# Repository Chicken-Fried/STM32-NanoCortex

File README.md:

<div align="center">

# ⚡ NanoCortex-F042
### by CaveRover

**Minimalist ARM Cortex-M0 development board — 20 mm × 38.5 mm, native USB-C, crystal-less**

[🇫🇷 Version française](README_FR.md) · [📄 Schematic (PDF)](arm_tiny_pcb_sch.pdf) · [🧰 Getting started](#getting-started) · [📌 Pinout](#pinout)

</div>

---

A practical, standalone 32-bit development board (**20 mm × 38.5 mm**), inspired by the minimalist philosophy and straightforward nature of the Arduino ATtiny, but optimized for comfortable benchtop development (*devboard*). Powered by the **STM32F042** (ARM Cortex-M0) with native crystal-less USB-C, a **TVS-protected** USB input and a **ceramic-only 3.3 V power stage**.

---

## 🌟 Why This Project?

This board was born at the intersection of academic learning, curiosity, and maker passion:

1. **Bridging Theory and Practice:** Taking electronic engineering coursework (schematic design, component selection, signal integrity, PCB layout) and applying it to a tangible, physical board.
2. **Stepping into 32-bit Microcontrollers:** Moving beyond traditional 8-bit platforms (AVR, ATtiny) into the modern ARM Cortex ecosystem.
3. **Fun & Hobby:** A passion-driven learning playground to experiment with USB stacks, low-power modes, and embedded programming.
4. **Giving Back to Open Source:** Providing a clean, accessible, and minimal reference design for students, hobbyists, and makers.
5. **Real-World Project Stepping Stone:** Serving as the core validation platform for three concrete engineering builds: a dedicated **drone telemetry/control subsystem**, an **audio synthesizer with active analog op-amp (AOP) filtering**, and a **digitally controlled $\ge$ 40W USB-PD / Buck converter power stage**.

---

## ✨ Key Features

* **🧠 Brain:** STMicroelectronics **STM32F042F6P6** (ARM Cortex-M0 @ 48 MHz, 32 KB Flash, 6 KB RAM).
* **🔌 Crystal-less USB-C:** Employs the internal 48 MHz oscillator (`HSI48`) paired with Clock Recovery System (`CRS`) synchronized directly to USB frames—**zero external crystal required**.
* **🚀 Zero-Programmer Flashing (Native DFU):** Factory ROM USB bootloader built-in. Hold the `BOOT` button, plug in the USB-C cable, and flash directly with `STM32CubeProgrammer` or `dfu-util`—no ST-Link or external programmer strictly required!
* **📐 Compact Devboard Layout (20 mm × 38.5 mm):** Slim form factor with two 9-pin I/O headers on the long sides, and the `BOOT` / `RESET` buttons on each side of the USB-C connector.
* **🛡️ Enhanced USB Protection:** **SD05-01FTG** TVS diode on `VBUS`, **USBLC6-2SC6** on the data lines and a 500 mA resettable polyfuse.
* **⚡ Stable 3.3 V:** **ME6211C33M5G-N** low-dropout, low-quiescent-current LDO, stable with small **ceramic capacitors** (no more tantalum).
* **💡 Two Indicator LEDs:** a red `3V3` power LED and an addressable **WS2812B-2020-V6** RGB `STATUS` LED driven from `PA0` (native 3.3 V operation with dedicated 100 nF decoupling capacitor `C8`).
* **🎛️ Dual Tactile Buttons:** On-board `RESET` and `BOOT` tactile switches for instant programming mode entry.
* **🛰️ CaveRover Branding:** Features the official 8-bit pixel art CaveRover rover silkscreen emblem and futuristic Anurati typographic markings directly on the PCB.
* **🛠️ Open-Source & DIY Ready:** Standard 2-layer PCB design rules for affordable fabrication and assembly (e.g. JLCPCB).

---

## 📋 Specifications

| Parameter | Specification |
| :--- | :--- |
| **Microcontroller** | STM32F042F6P6 (TSSOP-20) |
| **Core Architecture** | ARM 32-bit Cortex-M0 @ up to 48 MHz |
| **Flash / SRAM** | 32 KB Flash / 6 KB SRAM |
| **Operating Voltage** | 3.3 V logic (Dual power rails exposed: 5 V via USB-C + 3.3 V regulated) |
| **3.3 V Regulator** | ME6211C33M5G-N (LDO, SOT-23-5) with 2 ceramic capacitors (X7R, 25 V, 0805) |
| **Input Protection** | SD05-01FTG (TVS) + USBLC6-2SC6 (USB data lines) + 500 mA polyfuse |
| **USB Interface** | USB 2.0 Full Speed (12 Mbps) over USB-C |
| **User I/O** | 12 GPIOs on 2.54 mm headers (9 general-purpose, 1 shared with BOOT0, 2 shared with SWD) + dedicated hardware `NRST` |
| **Programming & Debug** | Native USB DFU (ROM bootloader) or full 4-wire SWD (`GND`, `NRST`, `SWDIO`, `SWCLK`) |
| **On-board LEDs** | Red `3V3` power LED + WS2812B-2020-V6 RGB status LED (`PA0`) with 100 nF decoupling capacitor |
| **Dimensions** | **20 mm × 38.5 mm** |

---

## 📌 Pinout

The board has two 9-pin headers (`J1` on the left, `J2` on the right) and a 2 × 2 power header (`J3`) at the bottom edge.

| Header | Pin | Signal | MCU pin | Primary & Alternate Functions / Notes |
| :---: | :---: | :--- | :--- | :--- |
| **J1** | 1 | `5V` | – | 5.0 V power rail (VBUS post-polyfuse `F1`, up to 500 mA for drones/op-amps) |
| | 2 | `GPIO1` | `PB8` | Shared with `BOOT0` (10 kΩ pull-down). **Do not pull HIGH at boot!** |
| | 3 | `GPIO2` | `PF0` | `OSC_IN` / I2C1_SDA |
| | 4 | `GPIO3` | `PF1` | `OSC_OUT` / I2C1_SCL |
| | 5 | `GPIO5` | `PA1` | `ADC_IN1` / TIM2_CH2 / EVENTOUT |
| | 6 | `GPIO6` | `PA2` | `USART2_TX` / `ADC_IN2` / TIM15_CH1 / TIM2_CH3 |
| | 7 | `GPIO7` | `PA3` | `USART2_RX` / `ADC_IN3` / TIM15_CH2 / TIM2_CH4 |
| | 8 | `GPIO8` | `PA4` | `ADC_IN4` / SPI1_NSS / TIM14_CH1 |
| | 9 | `GND` | – | Ground |
| **J2** | 1 | `3V3` | – | 3.3 V regulated power rail |
| | 2 | `GPIO9` | `PA5` | `ADC_IN5` / SPI1_SCK |
| | 3 | `GPIO10` | `PA6` | `ADC_IN6` / SPI1_MISO / TIM3_CH1 / TIM16_CH1 |
| | 4 | `GPIO11` | `PA7` | `ADC_IN7` / SPI1_MOSI / TIM3_CH2 / TIM14_CH1 / TIM17_CH1 |
| | 5 | `GPIO12` | `PB1` | `ADC_IN9` / TIM3_CH4 / TIM14_CH1 |
| | 6 | `GND` | – | Ground |
| | 7 | `NRST` | Pin 4 | Hardware Reset line (supports ST-Link "Connect Under Reset" and remote reset button) |
| | 8 | `GPIO15` | `PA13` | `SWDIO` (SWD Data) / IR_OUT / USB_NOE |
| | 9 | `GPIO16` | `PA14` | `SWCLK` (SWD Clock) / USART2_TX |
| **J3** | 1–4 | `3V3` / `GND` | – | 2 × 2 header: 2 × `3V3`, 2 × `GND` (auxiliary power breakout) |

> ⚠️ **Important Note on `PB8 / BOOT0` (`GPIO1`):** Pin 1 of the TSSOP-20 package is shared between `BOOT0` and `PB8`. It is pulled down to GND via $R_7$ (10 kΩ) for normal Flash execution. Any external circuitry attached to `GPIO1` that pulls this pin HIGH at reset will force the microcontroller into native USB DFU bootloader mode.
>
> 💡 **Internal Signals & ADC Allocation:**
> * `PA0` is dedicated internally to the **WS2812B-2020-V6** RGB status LED via $R_6$ (330 Ω). Consequently, analog channel `ADC_IN0` is reserved for on-board LED operation. **7 external ADC channels** remain freely available on the headers (`PA1` to `PA7`).
> * `NRST` is wired to the tactile `RESET` button with a 100 nF debounce capacitor and routed to `J2` pin 7 for full debugger control.
>
> 🔌 **Serial Communication (`USART1` vs `USART2`):**
> * For user serial communication (e.g. drone CRSF/SBUS telemetry, debug console, GPS), **use `USART2` (`PA2`/`PA3`) on header `J1`**.
> * On the STM32F042 TSSOP-20 package, `USART1` (`PA9`/`PA10`) shares physical pins 17 & 18 with native USB Full-Speed (`PA11`/`PA12`, `USB_DM`/`USB_DP`). When USB is active, `USART1` cannot be used simultaneously.

---

## 🛠️ Hardware Overview

> 🔎 **Click the schematic to open the full-resolution vector PDF** → [`arm_tiny_pcb_sch.pdf`](arm_tiny_pcb_sch.pdf)

### Power & Protection
* **USB-C Input:** Standard Type-C receptacle (GT-USB-7025) with dual 5.1 kΩ pull-downs on `CC1`/`CC2` for universal charger and PC host compatibility.
* **TVS Diode (SD05-01FTG, D1):** Clamps ESD and surge events on `VBUS` (5 V) before they can reach the rest of the board.
* **Polyfuse (F1, 500 mA):** Resettable fuse between `VBUS` and the 5 V rail.
* **USB Data Protection (USBLC6-2SC6, U3):** Low-capacitance ESD protection on `D+` / `D-`, preserving Full-Speed signal integrity.
* **LDO Regulator (ME6211C33M5G-N, LDO1):** 5 V → 3.3 V, low dropout and very low quiescent current.
* **Ceramic-Only Capacitors:** Tantalum capacitors were replaced by **X7R ceramic capacitors** (`C1` 2.2 µF, `C2` 1 µF, 25 V, 0805) around the regulator: more stable with this LDO, smaller, non-polarized, and free of tantalum failure modes (inrush / surge).
* **Decoupling:** `C3` 100 nF, `C4` 4.7 µF, `C5` 10 nF and `C6` 1 µF placed close to the `VDD` / `VDDA` pins.

### Signal Routing
* **Differential USB Pair:** Matched $D^+$ and $D^-$ traces routed side-by-side with an unbroken ground reference plane on the bottom layer to maintain high signal integrity.

---

## 🧾 Key Components

| Ref | Part | Function |
| :--- | :--- | :--- |
| U1 | STM32F042F6P6 | Microcontroller (TSSOP-20) |
| LDO1 | ME6211C33M5G-N | 3.3 V LDO regulator (SOT-23-5) |
| U3 | USBLC6-2SC6 | ESD protection for USB data lines |
| D1 | SD05-01FTG | 5 V TVS diode on `VBUS` (SOD-323) |
| F1 | JK-SMD0603-050-6 | 0603 resettable fuse (500 mA) |
| USB1 | GT-USB-7025 | USB Type-C receptacle |
| SW1 / SW2 | SKRKAEE020 | `RESET` / `BOOT` tactile switches |
| LED1 | 16-213/BHC-AN1P2/3T | Red `3V3` power LED |
| LED2 | WS2812B-2020-V6 | RGB `STATUS` LED (addressable) |
| J1 / J2 / J3 | 1×9 / 1×9 / 2×2 pin headers | I/O and power headers |

---

## 📝 Revision History

| Change | Before | Now |
| :--- | :--- | :--- |
| **Board size** | 26 mm × 36 mm | **20 mm × 38.5 mm** |
| **LDO regulator** | XBL1117-3.3 (SOT-89) | **ME6211C33M5G-N** (SOT-23-5) |
| **Regulator capacitors** | Tantalum (EIA-3528) | **X7R ceramic (0805)** |
| **5 V input protection** | Fuse only | Fuse + **SD05-01FTG TVS diode** |

---

## 💻 Getting Started & Programming

### 1. Entering Native USB DFU Mode
No external probe needed:
1. Hold down the **BOOT** button.
2. Press and release the **RESET** button (or plug the USB-C cable into your PC).
3. Release the **BOOT** button.
4. Your computer now recognizes the device as an **STM32 BOOTLOADER** in DFU mode.

### 2. Flashing
Flash compiled `.bin` or `.hex` firmware using your tool of choice:
* **STM32CubeProgrammer** (GUI / CLI)
* **dfu-util:**
  ```bash
  dfu-util -a 0 -d 0483:df11 --dfuse-address 0x08000000 -D firmware.bin
  ```
* **SWD (optional):** connect an ST-Link to `GND`, `3V3`, `PA13` (`SWDIO`) and `PA14` (`SWCLK`) on `J1` / `J2`.

### 3. Firmware Support
* **STM32CubeIDE / Keil / IAR:** Native C/C++ development with STM32 HAL / LL drivers.
* **PlatformIO & Arduino:** Fully compatible via the official [STM32duino Core](https://github.com/stm32duino/Arduino_Core_STM32).

---

## 📁 Repository Content

| File / Folder | Description |
| :--- | :--- |
| [`arm_tiny_pcb.kicad_pro`](arm_tiny_pcb.kicad_pro) | KiCad project (open this one) |
| [`arm_tiny_pcb.kicad_sch`](arm_tiny_pcb.kicad_sch) | KiCad schematic |
| [`arm_tiny_pcb.kicad_pcb`](arm_tiny_pcb.kicad_pcb) | KiCad PCB layout |
| [`arm_tiny_pcb_sch.pdf`](arm_tiny_pcb_sch.pdf) | Schematic export (PDF) |
| [`arm_tiny_pcb.jpg`](arm_tiny_pcb.jpg) | 3D render of the board (full size) |
| [`docs/`](docs) | Images used in this README (top view, bottom view, 3D perspective, schematic preview, branding) |
| [`NanoCortex.kicad_sym`](NanoCortex.kicad_sym) | Project symbol library |
| [`NanoCortex.pretty/`](NanoCortex.pretty) | Project footprint library |
| [`NanoCortex.3dshapes/`](NanoCortex.3dshapes) | 3D models (`.wrl`) for the project footprints |
| `sym-lib-table`, `fp-lib-table` | Project library tables (paths relative to the project) |

> 📦 **Libraries:** everything needed to open the project is included. The `NanoCortex` libraries are registered automatically when you open `arm_tiny_pcb.kicad_pro` with **KiCad 10**.

---

## 🎯 Roadmap & Target Application Projects

This board serves as the prototyping brain for three dedicated embedded hardware projects:

### 🛸 Track 1: Lightweight Drone Subsystem & Telemetry Board
Using the NanoCortex-F042 as an embedded flight module or motor/sensor companion node:
- [ ] **Sensor Interface:** High-rate 6-axis IMU (gyro/accelerometer via SPI/I2C) readout on hardware timer interrupts.
- [ ] **Actuator Control:** Multi-channel high-speed motor control signals (OneShot / DShot / PWM at 400 Hz+).
- [ ] **Telemetry & Communication:** Real-time bi-directional link over serial UART (`USART2` running CRSF / SBUS / MSP protocol).
- [ ] **Custom PCB Spin:** Layout of a dedicated, miniaturized drone PCB integrating motor drivers and power management.

### 🎛️ Track 2: Hybrid USB-MIDI Synthesizer & Analog Op-Amp Audio Lab
A hands-on project to master operational amplifiers (Op-Amps / AOP) and USB communication without requiring heavy DSP:
- [ ] **USB-MIDI Communication:** Native class-compliant USB-MIDI device stack (plug-and-play with DAWs, keyboards, and PCs with zero drivers).
- [ ] **Sound Generation:** Multi-waveform oscillator (sawtooth, square, triangle, wavetable) generated via high-frequency hardware PWM / DMA.
- [ ] **Active Op-Amp Reconstruction Filter:** 2nd- or 4th-order active low-pass filter (Sallen-Key / Rauch topology) to smooth PWM into clean analog audio.
- [ ] **Analog Processing & Overdrive Stage:** Soft-clipping diode distortion stage within the op-amp feedback loop (classic overdrive pedal architecture) with active gain control.
- [ ] **Active Tone Control & Output Stage:** Active Baxandall bass/treble tone stack and low-impedance audio buffer for headphones or line-level output.

### ⚡ Track 3: Digitally-Controlled Buck Converter & 40W+ USB-PD Lab
A hands-on power electronics project to master switch-mode power supplies (Buck converters), op-amp feedback injection, and USB Power Delivery:
- [ ] **Synchronous Buck Stage:** Design of an external 24 V DC → 5 V–20 V / 3 A step-down converter (MOSFET selection, inductor saturation $I_{sat}$, and low-ESR ripple filtering).
- [ ] **Op-Amp Feedback Injection:** Dynamic voltage margin/target control via active op-amp summing into the Buck controller's feedback (`FB`) node.
- [ ] **USB-PD PHY Communication (FUSB302B):** I2C control of a dedicated USB-PD Source controller to negotiate 5 V, 9 V, 15 V, and 20 V profiles with laptops and phones.
- [ ] **Power Telemetry & Safety:** Real-time $V_{out}$ / $I_{out}$ monitoring via STM32 12-bit ADC, over-current/over-voltage shutdown, and $V_{BUS}$ power-switch control.

### 🧪 Board Validation Milestones
- [x] KiCad 10 schematic design & 2-layer PCB layout with matched USB differential pairs.
- [x] Hardware Revision: 20 mm × 38.5 mm form factor, TVS protection diode, ME6211 LDO, and MLCC ceramic capacitors.
- [ ] PCB fabrication and prototype SMD assembly.
- [ ] USB DFU bootloader and crystal-less CRS clock verification.
- [ ] 3.3 V power rail validation (ripple, stability, and transient response under load).

---

## 🤝 Contributing & Feedback

Suggestions, questions, and PRs are very welcome! Whether you are a student exploring embedded design or an experienced engineer with layout tips, feel free to open an **Issue** or submit a **Pull Request**.

---

## 📜 License

This hardware design (schematics, PCB layout, footprints, and 3D models) is licensed under the **[CERN Open Hardware Licence Version 2 – Strongly Reciprocal (CERN-OHL-S v2)](LICENSE)**.

> ⚖️ **Reciprocal Sharing:** You are free to study, modify, build, and distribute this board. If you distribute modified versions or products based on this design, you must make the complete modified source files available under the same **CERN-OHL-S v2** license.

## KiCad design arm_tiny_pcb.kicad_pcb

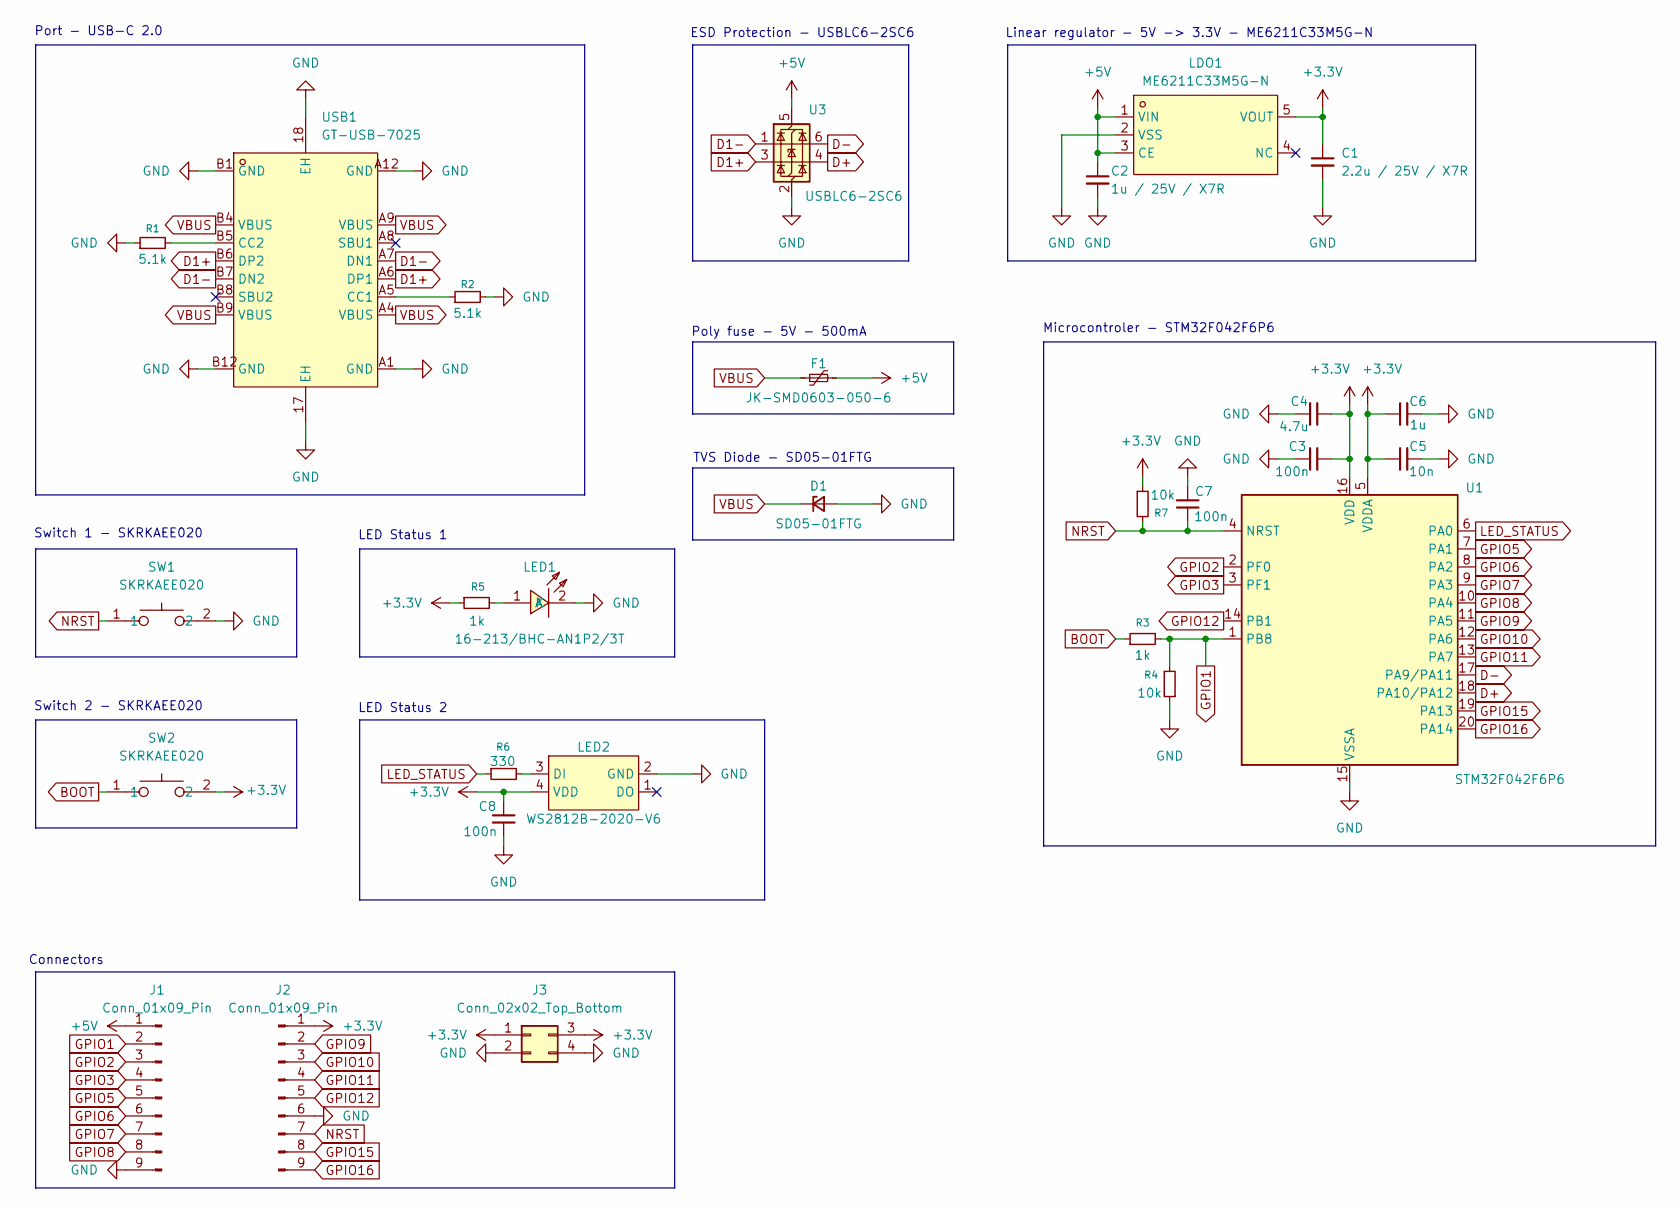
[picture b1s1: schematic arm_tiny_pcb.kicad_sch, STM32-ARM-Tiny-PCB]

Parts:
C1: 2.2u / 25V / X7R; C_0805_2012Metric; LCSC Part C22409262
C2: 1u / 25V / X7R; C_0805_2012Metric; LCSC Part C2171577
C3, C7, C8: 100n; C_0402_1005Metric
C4: 4.7u; C_0402_1005Metric; LCSC Part C368809
C5: 10n; C_0402_1005Metric; LCSC Part C307329
C6: 1u; C_0402_1005Metric; LCSC Part C29266
D1: SD05-01FTG; SOD-323_L1.8-W1.3-LS2.5-RD; LCSC Part C426873
F1: JK-SMD0603-050-6; F0603; LCSC Part C2832203
J1, J2: Conn_01x09_Pin; PinHeader_1x09_P2.54mm_Vertical; LCSC Part C42372501
J3: Conn_02x02_Top_Bottom; PinHeader_2x02_P2.54mm_Vertical; LCSC Part C124362
LDO1: ME6211C33M5G-N; SOT-23-5_L3.0-W1.7-P0.95-LS2.8-BL; MPN ME6211C33M5G-N; LCSC Part C82942
LED1: 16-213/BHC-AN1P2/3T; LED0402-R-RD; MPN 16-213/BHC-AN1P2/3T; LCSC Part C131223
LED2: WS2812B-2020-V6; LED-SMD_4P-L2.2-W2.0-P1.00_WS2815C-2020-4P; MPN WS2812B-2020-V6; LCSC Part C52917434
R1, R2: 5.1k; R_0402_1005Metric; LCSC Part C278598
R3, R5: 1k; R_0402_1005Metric; LCSC Part C71623
R4, R7: 10k; R_0402_1005Metric; LCSC Part C71617
R6: 330; R_0402_1005Metric; LCSC Part C140196
SW1, SW2: SKRKAEE020; SW-SMD_L3.9-W3.0-P4.45; MPN SKRKAEE020; LCSC Part C115357
U1: STM32F042F6P6; TSSOP-20_4.4x6.5mm_P0.65mm; LCSC Part C81000
U3: USBLC6-2SC6; SOT-23-6; LCSC Part C7519
USB1: GT-USB-7025; TYPE-C-SMD_GT-USB-7025; MPN GT-USB-7025; LCSC Part C963213

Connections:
+3.3V: C1.1, C3.2, C4.2, C5.1, C6.1, C8.2, J2.1, J3.1, J3.3, LDO1.5 (VOUT), LED2.4 (VDD), R5.1, R7.1, SW2.2, U1.5 (VDDA), U1.16 (VDD)
+5V: C2.1, F1.2, J1.1, LDO1.1 (VIN), LDO1.3 (CE), U3.5 (VBUS)
BOOT: R3.1, SW2.1
D1+: U3.3 (I/O2), USB1.A6 (DP1), USB1.B6 (DP2)
D1-: U3.1 (I/O1), USB1.A7 (DN1), USB1.B7 (DN2)
D+: U1.18 (PA10/PA12), U3.4 (I/O2)
D-: U1.17 (PA9/PA11), U3.6 (I/O1)
GND: C1.2, C2.2, C3.1, C4.1, C5.2, C6.2, C7.2, C8.1, D1.2 (A), J1.9, J2.6, J3.2, J3.4, LDO1.2 (VSS), LED1.2 (K), LED2.2 (GND), R1.1, R2.2, R4.1, SW1.2, U1.15 (VSSA), U3.2 (GND), USB1.17 (EH), USB1.18 (EH), USB1.A1 (GND), USB1.A12 (GND), USB1.B1 (GND), USB1.B12 (GND)
GPIO1: J1.2, R3.2, R4.2, U1.1 (PB8)
GPIO2: J1.3, U1.2 (PF0)
GPIO3: J1.4, U1.3 (PF1)
GPIO5: J1.5, U1.7 (PA1)
GPIO6: J1.6, U1.8 (PA2)
GPIO7: J1.7, U1.9 (PA3)
GPIO8: J1.8, U1.10 (PA4)
GPIO9: J2.2, U1.11 (PA5)
GPIO10: J2.3, U1.12 (PA6)
GPIO11: J2.4, U1.13 (PA7)
GPIO12: J2.5, U1.14 (PB1)
GPIO15: J2.8, U1.19 (PA13)
GPIO16: J2.9, U1.20 (PA14)
LED_STATUS: R6.1, U1.6 (PA0)
NRST: C7.1, J2.7, R7.2, SW1.1, U1.4 (NRST)
unnamed: LED1.1 (A), R5.2
unnamed: LED2.3 (DI), R6.2
unnamed: R2.1, USB1.A5 (CC1)
unnamed: R1.2, USB1.B5 (CC2)
VBUS: D1.1 (K), F1.1, USB1.A4 (VBUS), USB1.A9 (VBUS), USB1.B4 (VBUS), USB1.B9 (VBUS)

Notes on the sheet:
Poly fuse - 5V - 500mA
LED Status 2
Switch 1 - SKRKAEE020
LED Status 1
Microcontroler - STM32F042F6P6
TVS Diode - SD05-01FTG
Switch 2 - SKRKAEE020
Linear regulator - 5V -> 3.3V - ME6211C33M5G-N
Connectors
Port - USB-C 2.0
ESD Protection - USBLC6-2SC6

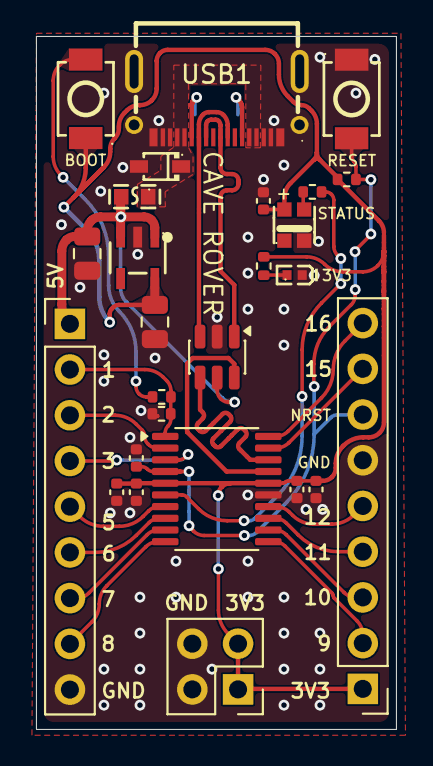
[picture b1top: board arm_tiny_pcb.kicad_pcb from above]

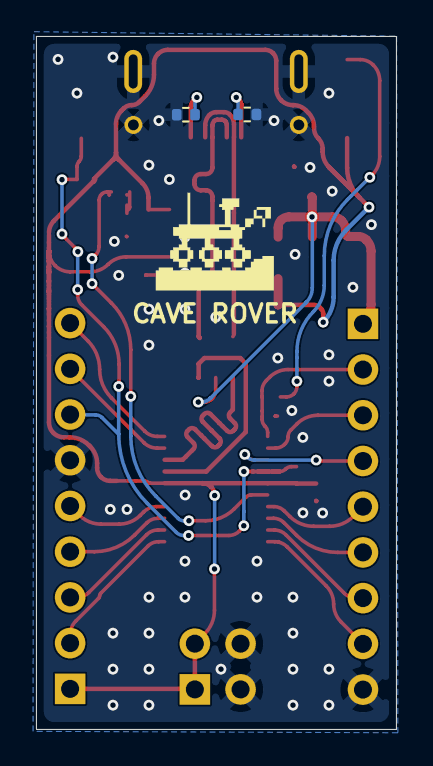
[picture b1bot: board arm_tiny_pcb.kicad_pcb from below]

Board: 2 copper layers, 20.0 x 38.5 mm, 29 parts (3 on the bottom side), 28 nets.

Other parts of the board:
LOGO**: Logo_CavityRover_F_SilkS; Logo_CavityRover

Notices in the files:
README.md:
License: CERN-OHL-S-2.0
